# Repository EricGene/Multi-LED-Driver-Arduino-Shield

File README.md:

# Multi-LED-Driver-Arduino-Shield
The circuit uses BJT NPNs to control three color changing LEDs.  The Arduino provides bias current to switch the transistor between saturation and cut-off modes.

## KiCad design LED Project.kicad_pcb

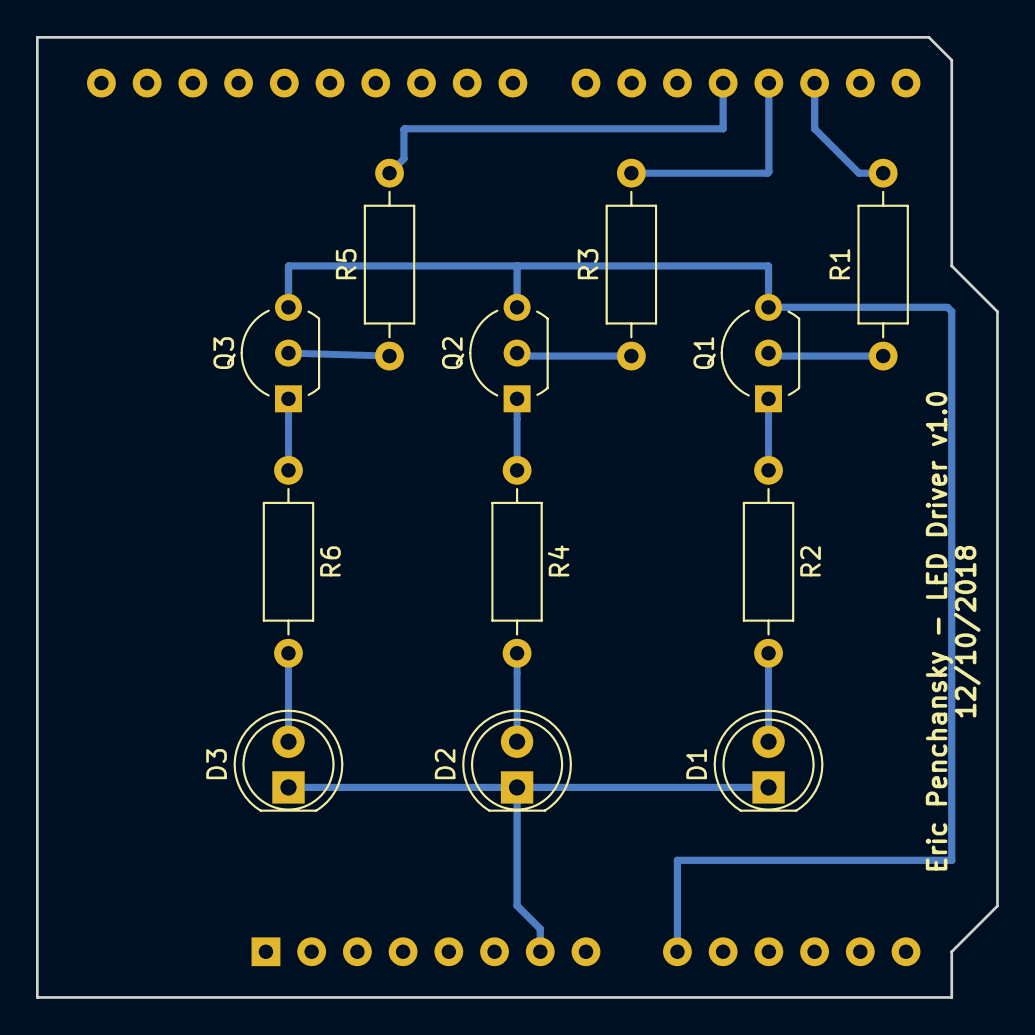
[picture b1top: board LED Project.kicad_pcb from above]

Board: 2 copper layers, 53.3 x 53.3 mm, 13 parts (1 on the bottom side), 14 nets.

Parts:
A1: Arduino_UNO_R3
D1, D2, D3: LED; LED_D5.0mm
Q1, Q2, Q3: 2N3904; TO-92L_Inline_Wide
R1, R3, R5: 1k; R_Axial_DIN0207_L6.3mm_D2.5mm_P10.16mm_Horizontal
R2, R4, R6: 180; R_Axial_DIN0207_L6.3mm_D2.5mm_P10.16mm_Horizontal

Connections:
GND: A1.7, D1.1, D2.1, D3.1
unnamed: A1.9, Q1.3, Q2.3, Q3.3
unnamed: A1.17, R1.2
unnamed: A1.18, R3.2
unnamed: A1.19, R5.2
unnamed: D1.2, R2.2
unnamed: D2.2, R4.2
unnamed: D3.2, R6.2
unnamed: Q1.1, R2.1
unnamed: Q1.2, R1.1
unnamed: Q2.1, R4.1
unnamed: Q2.2, R3.1
unnamed: Q3.1, R6.1
unnamed: Q3.2, R5.1
